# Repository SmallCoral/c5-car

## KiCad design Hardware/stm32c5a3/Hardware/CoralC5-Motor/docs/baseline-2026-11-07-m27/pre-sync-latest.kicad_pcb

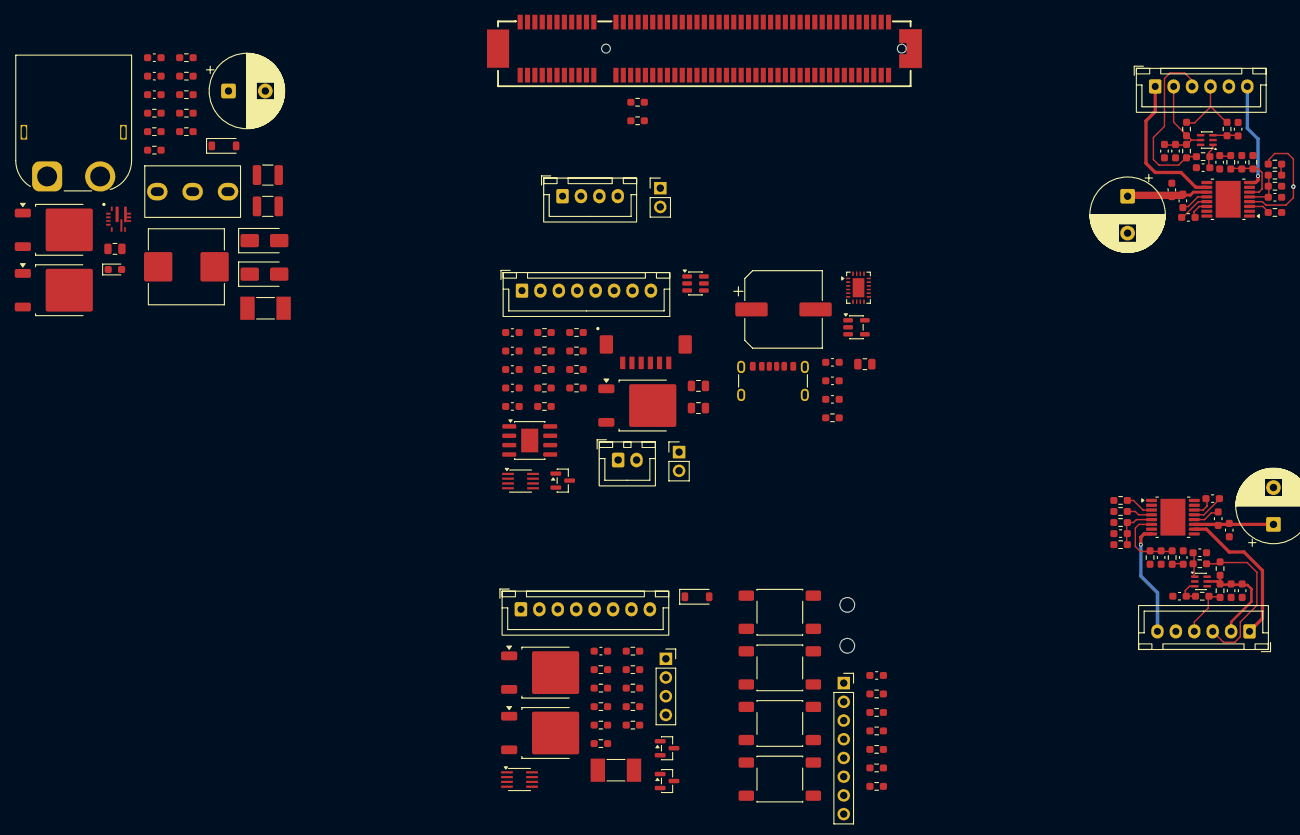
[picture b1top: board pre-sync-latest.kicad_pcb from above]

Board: 2 copper layers, 147 parts (0 on the bottom side), 108 nets.

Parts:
C1, C13, C33: 470u / 25V; Capacitor_THT__CP_Radial_D10.0mm_P5.00mm
C2: 10uF/50V X7R; Capacitor_SMD__C_0805_2012Metric
C3, C72, C76, C79, C80, C82: 100nF/50V; C_0603_1608Metric_Gap0.85mm_HandSolder
C4: 100nF/16V; C_0603_1608Metric_Gap0.85mm_HandSolder
C5, C50: 22uF/25V X7R; Capacitor_SMD__C_1210_3225Metric
C10, C30: 22n / 50V; C_0603_1608Metric_Gap0.85mm_HandSolder
C11, C14, C16, C19, C31, C34, C36, C39: 100n / 16V; C_0603_1608Metric_Gap0.85mm_HandSolder
C12, C32: 100n / 50V; C_0603_1608Metric_Gap0.85mm_HandSolder
C15, C35: 10n / 16V; C_0603_1608Metric_Gap0.85mm_HandSolder
C17, C18, C37, C38: 1n / 16V; C_0603_1608Metric_Gap0.85mm_HandSolder
C20, C40: 1u / 10V; C_0603_1608Metric_Gap0.85mm_HandSolder
C54, C55: 1uF/10V X7R; C_0603_1608Metric_Gap0.85mm_HandSolder
C56: 100nF/10V; C_0603_1608Metric_Gap0.85mm_HandSolder
C62, C78: 10uF/10V; Capacitor_SMD__C_0805_2012Metric
C63: 150pF/50V C0G; C_0603_1608Metric_Gap0.85mm_HandSolder
C73: 12nF/50V; C_0603_1608Metric_Gap0.85mm_HandSolder
C77: 1nF/50V; C_0603_1608Metric_Gap0.85mm_HandSolder
C81: 150uF/16V; Capacitor_SMD__CP_Elec_10x7.9
C83: 10uF/10V X7R; Capacitor_SMD__C_0805_2012Metric
D1: BZT52C12; Diode_SMD__D_SOD-123
D2: SMAJ15A; Diode_SMD__D_SMA
D3: SS34; Diode_SMD__D_SMA
D4: LED_GREEN; LED_0603_1608Metric_Gap0.85mm_HandSolder
D5: 12V; Diode_SMD__D_SOD-123
F1: 15A/85V FAST; Fuse_Littelfuse_448_6.10x2.69mm_GenericBody
F2: 4A / 125V 延时; Fuse_NANO2_454_6.10x2.69mm
H1, H2: TFT孔 D2.0; MountingHole__MountingHole_2mm
J1: XT60PW-M; AMASS_XT60PW-M_1x02_P7.20mm_Horizontal
J4, J6: MG513 / XH2.50 / 6P; Connector_JST__JST_XH_B6B-XH-A_1x06_P2.50mm_Vertical
J8: SWD / XH2.50; Connector_JST__JST_XH_B4B-XH-A_1x04_P2.50mm_Vertical
J10: RUN / STOP_NC; Connector_PinHeader_2.54mm__PinHeader_1x02_P2.54mm_Vertical
J14: C5-EDGE-3 / 98P; C5_EDGE_3_Socket
J15: HC-08_四脚接口; Connector_PinSocket_2.54mm__PinSocket_1x04_P2.54mm_Vertical
J17: TFT_ZJY180S0800TG01; Connector_PinSocket_2.54mm__PinSocket_1x08_P2.54mm_Vertical
J19: MaixCAM2_6P; ZX_MX1.25_6PWT
J20: 灰度并行_CH1-CH8; Connector_JST__JST_XH_B8B-XH-A_1x08_P2.50mm_Vertical
J21: 灰度电源_GND+5V; Connector_JST__JST_XH_B2B-XH-A_1x02_P2.50mm_Vertical
J23: ZDT_XS_TTL_8P; Connector_JST__JST_XH_B8B-XH-A_1x08_P2.50mm_Vertical
J27: 供电使能跳线; Connector_PinHeader_2.54mm__PinHeader_1x02_P2.54mm_Vertical
J28: Action4_USB_C_5V; Connector_USB__USB_C_Receptacle_GCT_USB4125-xx-x_6P_TopMnt_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
L1: 3.3uH / 12A; Inductor_SMD__L_Wuerth_HCI-1050
Q1, Q2, Q5, Q6, Q7: DMP3007LK3-13; Package_TO_SOT_SMD__TO-252-2
Q4, Q9: BSS138BK; Package_TO_SOT_SMD__SOT-23
Q8: MMBT3904; Package_TO_SOT_SMD__SOT-23
R1, R14, R34, R77, R78, R80, R81, R84, R86, R87, R88, R89, R90: 100k; R_0603_1608Metric_Gap0.85mm_HandSolder
R2, R82: 4.7k; R_0603_1608Metric_Gap0.85mm_HandSolder
R3: 82k / 1%; R_0603_1608Metric_Gap0.85mm_HandSolder
R4, R10, R11, R30, R31: 10k / 1%; R_0603_1608Metric_Gap0.85mm_HandSolder
R5: 2.2k; R_0603_1608Metric_Gap0.85mm_HandSolder
R6: 100R; R_0603_1608Metric_Gap0.85mm_HandSolder
R7, R13, R18, R19, R33, R38, R39, R50, R51, R52, R53, R55, R56, R76, R83, R85: 10k; R_0603_1608Metric_Gap0.85mm_HandSolder
R12, R32: 1.82k / 1%; R_0603_1608Metric_Gap0.85mm_HandSolder
R15, R16, R17, R35, R36, R37: 1k; R_0603_1608Metric_Gap0.85mm_HandSolder
R59: 73.8k / 0.1%; R_0603_1608Metric_Gap0.85mm_HandSolder
R60: 10k / 0.1%; R_0603_1608Metric_Gap0.85mm_HandSolder
R68: 33.6k / 0.1%; R_0603_1608Metric_Gap0.85mm_HandSolder
R69, R71: 15k / 0.1%; R_0603_1608Metric_Gap0.85mm_HandSolder
R70: 42.2k / 0.1%; R_0603_1608Metric_Gap0.85mm_HandSolder
R72: 95.3k / 1%; R_0603_1608Metric_Gap0.85mm_HandSolder
R91: 100k / 1%; R_0603_1608Metric_Gap0.85mm_HandSolder
R92: 30.1k / 1%; R_0603_1608Metric_Gap0.85mm_HandSolder
SW1: SS12D10G5; SS12D10G5_SHOUHAN_3P_P4.80mm
SW2: 模式; SW_Push_6x6x4.3mm_SMD_4Pad_Generic
SW3: 下一项; SW_Push_6x6x4.3mm_SMD_4Pad_Generic
SW4: 确认; SW_Push_6x6x4.3mm_SMD_4Pad_Generic
SW5: 启动; SW_Push_6x6x4.3mm_SMD_4Pad_Generic
U1: TPS56837RPAR; Texas_RPA0010A_HotRod_3x3
U2, U4: DRV8874PWPR; DRV8874_PWP0016
U3, U5: SN74LVC2G17DCKR; Package_TO_SOT_SMD__SOT-363_SC-70-6
U7: AP2112K-3.3TRG1; Package_TO_SOT_SMD__SOT-23-5
U10: SGM2531CXPS8G/TR; SGM_PS8_SOIC8_EP2.33x3.22_HandSolder
U13, U15: SN74LVC2G125DCTR; Package_SO__SSOP-8_2.95x2.8mm_P0.65mm
U14: LTC4412ES6#TRMPBF; Package_TO_SOT_SMD__TSOT-23-6
U16: TPS25810RVCR; Package_DFN_QFN__Texas_RVC0020A_WQFN-20-1EP_3x4mm_P0.5mm_EP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

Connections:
/V3V3: C19.1, C20.1, C39.1, C40.1, C76.1, C80.1, J4.2 (VENC), J6.2 (VENC), J8.1, J14.A47 (A47_/_+3V3), J14.B47 (B47_/_+3V3), R10.1, R13.2, R18.1, R19.2, R30.1, R33.2, R38.1, R39.2, R50.1, R51.1, R52.1, R53.1, R76.1, R80.1, R85.1, R88.1, U3.5 (VCC), U5.5 (VCC), U13.8 (VCC), U15.8 (VCC)
/V3V3_EXT: C55.1, C56.1, J15.1 (3V3), J17.2 (VCC_3V3), R55.1, R56.1, U7.5 (VOUT)
/V5_EXT: C5.1, C54.1, C63.1, C72.1, C78.1, C81.1, C82.1, D3.2 (A), J21.2 (+5V), J27.1 (5V), L1.2, R59.1, R70.1, U7.1 (VIN), U7.3 (EN), U10.4 (IN), U16.2 (IN1), U16.3 (IN1), U16.4 (IN2), U16.5 (AUX), U16.6 (EN), U16.7 (CHG), U16.8 (CHG_HI)
/V5_SYS: D3.1 (K), J14.A48 (A48_/_+5V_SYS), J14.B48 (B48_/_+5V_SYS), R5.1
/VM: C1.1, C2.1, C3.1, C11.1, C12.1, C13.1, C31.1, C32.1, C33.1, C50.1, D2.1 (K), F2.1, Q2.2 (D), R3.1, U1.8 (VIN), U2.11 (VM), U4.11 (VM)
/中景园屏幕与四个操作按钮/KEY_MODE: J14.B7 (B7_/_PC4), R50.2, SW2.1
/中景园屏幕与四个操作按钮/KEY_NEXT: J14.B8 (B8_/_PC5), R51.2, SW3.1
/中景园屏幕与四个操作按钮/KEY_OK: J14.B11 (B11_/_PB2), R52.2, SW4.1
/中景园屏幕与四个操作按钮/KEY_START: J14.B12 (B12_/_PE7), R53.2, SW5.1
/中景园屏幕与四个操作按钮/TFT_BL: J14.A32 (A32_/_PB4), J17.8 (BL)
/中景园屏幕与四个操作按钮/TFT_CS: J14.B3 (B3_/_PA4), J17.7 (CS), R55.2
/中景园屏幕与四个操作按钮/TFT_DC: J14.B10 (B10_/_PB1), J17.6 (DC)
/中景园屏幕与四个操作按钮/TFT_MOSI: J14.B6 (B6_/_PA7), J17.4 (SDA)
/中景园屏幕与四个操作按钮/TFT_RES: J14.B9 (B9_/_PB0), J17.5 (RES), R56.2
/中景园屏幕与四个操作按钮/TFT_SCK: J14.B4 (B4_/_PA5), J17.3 (SCL)
/右电机与编码器/MOTOR_RUN: J10.2, R7.1, R14.1, R34.1, U2.3 (nSLEEP), U4.3 (nSLEEP)
/右电机与编码器/R_DIR: J14.A34 (A34_/_PD7), U4.2 (PH/IN2)
/右电机与编码器/R_ENC_A: J14.A33 (A33_/_PB3), U5.6 (1Y)
/右电机与编码器/R_ENC_B: J14.A45 (A45_/_PA15), U5.4 (2Y)
/右电机与编码器/R_ISENSE: C36.1, J14.A11 (A11_/_PC0), R35.2
/右电机与编码器/R_M_OUT1: J6.6 (M+), U4.8 (OUT1)
/右电机与编码器/R_M_OUT2: J6.1 (M-), U4.10 (OUT2)
/右电机与编码器/R_PWM: J14.A27 (A27_/_PB8), U4.1 (EN/IN1)
/右电机与编码器/R_nFAULT: J14.A35 (A35_/_PD6), R33.1, U4.4 (nFAULT)
/四脚蓝牙与外接步进驱动接口/BT_RX: J14.B2 (B2_/_PA3), J15.4 (TXD)
/四脚蓝牙与外接步进驱动接口/BT_TX: J14.A2 (A2_/_PA2), J15.3 (RXD)
/四脚蓝牙与外接步进驱动接口/STEP_PWR_EN: J14.B30 (B30_/_PD12), R83.1
/四脚蓝牙与外接步进驱动接口/STEP_UART_RX: J14.A29 (A29_/_PB7), U15.3 (2Y)
/四脚蓝牙与外接步进驱动接口/STEP_UART_TX: J14.A30 (A30_/_PB6), R88.2, U15.2 (1A)
/四脚蓝牙与外接步进驱动接口/VM_STEP: J23.1 (VM_V+), Q7.2 (D), R86.1
/左电机与编码器/L_DIR: J14.A8 (A8_/_PC3), U2.2 (PH/IN2)
/左电机与编码器/L_ENC_A: J14.A4 (A4_/_PA0), U3.6 (1Y)
/左电机与编码器/L_ENC_B: J14.A3 (A3_/_PA1), U3.4 (2Y)
/左电机与编码器/L_ISENSE: C16.1, J14.A5 (A5_/_PH5), R15.2
/左电机与编码器/L_M_OUT1: J4.6 (M+), U2.8 (OUT1)
/左电机与编码器/L_M_OUT2: J4.1 (M-), U2.10 (OUT2)
/左电机与编码器/L_PWM: J14.A9 (A9_/_PC2), U2.1 (EN/IN1)
/左电机与编码器/L_nFAULT: J14.A7 (A7_/_PH4), R13.1, U2.4 (nFAULT)
/核心板接口/GRAY_CH1: J14.B15 (B15_/_PE10), J20.1 (CH1)
/核心板接口/GRAY_CH2: J14.B16 (B16_/_PE11), J20.2 (CH2)
/核心板接口/GRAY_CH3: J14.B17 (B17_/_PE12), J20.3 (CH3)
/核心板接口/GRAY_CH4: J14.B18 (B18_/_PE13), J20.4 (CH4)
/核心板接口/GRAY_CH5: J14.B19 (B19_/_PE14), J20.5 (CH5)
/核心板接口/GRAY_CH6: J14.B20 (B20_/_PE15), J20.6 (CH6)
/核心板接口/GRAY_CH7: J14.B28 (B28_/_PD10), J20.7 (CH7)
/核心板接口/GRAY_CH8: J14.B29 (B29_/_PD11), J20.8 (CH8)
/核心板接口/MOTOR_EN_REQ: J14.B13 (B13_/_PE8), R6.1
/核心板接口/SWCLK: J8.3, J14.A46 (A46_/_PA14)
/核心板接口/SWDIO: J8.2, J14.B43 (B43_/_PA13)
/核心板接口/VIDEO_RX: J14.B35 (B35_/_PC7), U13.3 (2Y)
/核心板接口/VIDEO_TX: J14.B34 (B34_/_PC6), R80.2, U13.2 (1A)
/灰度与 MaixCAM2 识别/V5_MAIX_PROT: C62.1, J19.2 (5V_IN), Q4.1 (G), Q5.3 (S), R77.1, U14.6 (SENSE)
/输入、总开关与降压/SW_SOURCE: D1.1 (K), Q1.3 (S), Q2.3 (S), R1.2, SW1.1 (A)
GND: C1.2, C2.2, C3.2, C5.2, C12.2, C13.2, C14.2, C15.2, C16.2, C17.1, C18.2, C19.2, C20.2, C32.2, C33.2, C34.2, C35.2, C36.2, C37.1, C38.2, C39.2, C40.2, C50.2, C54.2, C55.2, C56.2, C62.2, C72.2, C73.2, C76.2, C77.2, C78.2, C79.2, C80.2, C81.2, C82.2, C83.2, D2.2 (A), D4.1 (K), J1.2 (GND), J4.5 (GND), J6.5 (GND), J8.4, J14.50 (MP1_/_GND), J14.51 (MP2_/_GND), J14.A1 (A1_/_GND), J14.A49 (A49_/_GND), J14.B1 (B1_/_GND), J14.B49 (B49_/_GND), J15.2 (GND), J17.1 (GND), J19.1 (GND), J19.MP, J21.1 (GND), J23.2 (GND), J28.A12 (GND), J28.B12 (GND), J28.SH (SHIELD), Q4.2 (S), Q8.2 (E), Q9.2 (S), R2.2, R4.2, R7.2, R11.2, R12.2, R14.2, R31.2, R32.2, R34.2, R60.2, R69.2, R71.2, R72.2, R77.2, R78.2, R84.2, R87.2, R89.2, R90.2, R92.2, SW2.2, SW3.2, SW4.2, SW5.2, U1.3 (AGND), U1.9 (PGND), U2.7 (IMODE), U2.9 (PGND), U2.15 (GND), U2.16 (PMODE), U2.17 (EP), U3.2 (GND), U4.7 (IMODE), U4.9 (PGND), U4.15 (GND), U4.16 (PMODE), U4.17 (EP), U5.2 (GND), U7.2 (GND), U10.1 (GND), U10.9 (EP_GND), U13.4 (GND), U14.2 (GND), U14.3 (CTL), U15.4 (GND), U16.12 (GND), U16.21 (EP_GND)
unnamed: C83.1, J28.A9 (VBUS), J28.B9 (VBUS), U16.14 (OUT), U16.15 (OUT)
unnamed: D1.2 (A), Q1.1 (G), Q2.1 (G), R1.1, SW1.2 (B)
unnamed: D4.2 (A), R5.2
unnamed: D5.2 (A), Q6.1 (G), Q7.1 (G)
unnamed: D5.1 (K), Q6.3 (S), Q7.3 (S), R81.1
unnamed: F1.1, J1.1 (BAT+)
unnamed: J4.3 (A), R16.1, R18.2
unnamed: J4.4 (B), R17.1, R19.1
unnamed: J6.3 (A), R36.1, R38.2
unnamed: J6.4 (B), R37.1, R39.1
unnamed: J10.1, R6.2
unnamed: J19.6 (UART4_RX), U13.6 (1Y)
unnamed: J19.5 (UART4_TX), R78.1, U13.5 (2A)
unnamed: J23.7 (R/A/H_RX), R90.1, U15.6 (1Y)
unnamed: J23.8 (T/B/L_TX), R89.1, U15.5 (2A)
unnamed: J27.2 (EN_FEED), R68.1
unnamed: J28.A5 (CC1), U16.11 (CC1)
unnamed: J28.B5 (CC2), U16.13 (CC2)
unnamed: F1.2, Q1.2 (D)
unnamed: Q4.3 (D), R76.2, U13.1 (nOE1), U13.7 (nOE2)
unnamed: C79.1, Q5.2 (D), U10.5 (OUT), U14.1 (VIN)
unnamed: Q5.1 (G), U14.5 (GATE)
unnamed: F2.2, Q6.2 (D)
unnamed: Q8.1 (B), R83.2, R84.1
unnamed: Q8.3 (C), R82.2
unnamed: Q9.3 (D), R85.2, U15.1 (nOE1), U15.7 (nOE2)
unnamed: Q9.1 (G), R86.2, R87.1
unnamed: R81.2, R82.1
unnamed: R2.1, SW1.3 (C)
unnamed: C4.1, U1.7 (BOOT)
unnamed: R3.2, R4.1, U1.1 (EN)
unnamed: C63.2, R59.2, R60.1, U1.2 (FB)
unnamed: R92.1, U1.10 (MODE)
unnamed: C4.2, L1.1, U1.6 (SW)
unnamed: C10.1, U2.13 (CPH)
unnamed: C10.2, U2.14 (CPL)
unnamed: C15.1, R12.1, R15.1, U2.6 (IPROPI)
unnamed: C11.2, U2.12 (VCP)
unnamed: C14.1, R10.2, R11.1, U2.5 (VREF)
unnamed: C17.2, R16.2, U3.1 (1A)
unnamed: C18.1, R17.2, U3.3 (2A)
unnamed: C30.1, U4.13 (CPH)
unnamed: C30.2, U4.14 (CPL)
unnamed: C35.1, R32.1, R35.1, U4.6 (IPROPI)
unnamed: C31.2, U4.12 (VCP)
unnamed: C34.1, R30.2, R31.1, U4.5 (VREF)
unnamed: C37.2, R36.2, U5.1 (1A)
unnamed: C38.1, R37.2, U5.3 (2A)
unnamed: C77.1, R68.2, R69.1, U10.3 (ENUV)
unnamed: R72.1, U10.7 (ILIM)
unnamed: R70.2, R71.1, U10.8 (OVP)
unnamed: C73.1, U10.2 (SS)
unnamed: R91.1, U16.10 (REF)
unnamed: R91.2, U16.9 (REF_RTN)

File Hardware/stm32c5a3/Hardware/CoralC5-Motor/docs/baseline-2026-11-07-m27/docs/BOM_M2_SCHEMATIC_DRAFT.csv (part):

reference,value,mpn,tolerance,footprint,datasheet,sheet,status
C1,470u / 25V,EEU-FR1E471,,Motor:Capacitor_THT__CP_Radial_D10.0mm_P5.00mm,,/输入、总开关与降压/,M2.6 schematic draft; PCB not updated; not production release
C2,10u / 50V,GRM21BR61H106KE43L,,Motor:Capacitor_SMD__C_0805_2012Metric,,/输入、总开关与降压/,M2.6 schematic draft; PCB not updated; not production release
C3,100n / 50V,,,Motor:C_0603_1608Metric_Gap0.85mm_HandSolder,,/输入、总开关与降压/,M2.6 schematic draft; PCB not updated; not production release
C4,100n / 16V,,,Motor:C_0603_1608Metric_Gap0.85mm_HandSolder,,/输入、总开关与降压/,M2.6 schematic draft; PCB not updated; not production release
C5,22u / 10V,GRM31CR71A226KE15L,,Motor:Capacitor_SMD__C_1206_3216Metric,,/输入、总开关与降压/,M2.6 schematic draft; PCB not updated; not production release
C6,22u / 10V,GRM31CR71A226KE15L,,Motor:Capacitor_SMD__C_1206_3216Metric,,/输入、总开关与降压/,M2.6 schematic draft; PCB not updated; not production release
C10,22n / 50V,,,Motor:C_0603_1608Metric_Gap0.85mm_HandSolder,,/左电机与编码器/,M2.6 schematic draft; PCB not updated; not production release
C11,100n / 16V,,,Motor:C_0603_1608Metric_Gap0.85mm_HandSolder,,/左电机与编码器/,M2.6 schematic draft; PCB not updated; not production release
C12,100n / 50V,,,Motor:C_0603_1608Metric_Gap0.85mm_HandSolder,,/左电机与编码器/,M2.6 schematic draft; PCB not updated; not production release
C13,470u / 25V,EEU-FR1E471,,Motor:Capacitor_THT__CP_Radial_D10.0mm_P5.00mm,,/左电机与编码器/,M2.6 schematic draft; PCB not updated; not production release
C14,100n / 16V,,,Motor:C_0603_1608Metric_Gap0.85mm_HandSolder,,/左电机与编码器/,M2.6 schematic draft; PCB not updated; not production release
C15,10n / 16V,,,Motor:C_0603_1608Metric_Gap0.85mm_HandSolder,,/左电机与编码器/,M2.6 schematic draft; PCB not updated; not production release
C16,100n / 16V,,,Motor:C_0603_1608Metric_Gap0.85mm_HandSolder,,/左电机与编码器/,M2.6 schematic draft; PCB not updated; not production release
C17,1n / 16V,,,Motor:C_0603_1608Metric_Gap0.85mm_HandSolder,,/左电机与编码器/,M2.6 schematic draft; PCB not updated; not production release
C18,1n / 16V,,,Motor:C_0603_1608Metric_Gap0.85mm_HandSolder,,/左电机与编码器/,M2.6 schematic draft; PCB not updated; not production release
C19,100n / 16V,,,Motor:C_0603_1608Metric_Gap0.85mm_HandSolder,,/左电机与编码器/,M2.6 schematic draft; PCB not updated; not production release
C20,1u / 10V,,,Motor:C_0603_1608Metric_Gap0.85mm_HandSolder,,/左电机与编码器/,M2.6 schematic draft; PCB not updated; not production release
C30,22n / 50V,,,Motor:C_0603_1608Metric_Gap0.85mm_HandSolder,,/右电机与编码器/,M2.6 schematic draft; PCB not updated; not production release
C31,100n / 16V,,,Motor:C_0603_1608Metric_Gap0.85mm_HandSolder,,/右电机与编码器/,M2.6 schematic draft; PCB not updated; not production release
C32,100n / 50V,,,Motor:C_0603_1608Metric_Gap0.85mm_HandSolder,,/右电机与编码器/,M2.6 schematic draft; PCB not updated; not production release
C33,470u / 25V,EEU-FR1E471,,Motor:Capacitor_THT__CP_Radial_D10.0mm_P5.00mm,,/右电机与编码器/,M2.6 schematic draft; PCB not updated; not production release
C34,100n / 16V,,,Motor:C_0603_1608Metric_Gap0.85mm_HandSolder,,/右电机与编码器/,M2.6 schematic draft; PCB not updated; not production release
C35,10n / 16V,,,Motor:C_0603_1608Metric_Gap0.85mm_HandSolder,,/右电机与编码器/,M2.6 schematic draft; PCB not updated; not production release
C36,100n / 16V,,,Motor:C_0603_1608Metric_Gap0.85mm_HandSolder,,/右电机与编码器/,M2.6 schematic draft; PCB not updated; not production release
C37,1n / 16V,,,Motor:C_0603_1608Metric_Gap0.85mm_HandSolder,,/右电机与编码器/,M2.6 schematic draft; PCB not updated; not production release
C38,1n / 16V,,,Motor:C_0603_1608Metric_Gap0.85mm_HandSolder,,/右电机与编码器/,M2.6 schematic draft; PCB not updated; not production release
C39,100n / 16V,,,Motor:C_0603_1608Metric_Gap0.85mm_HandSolder,,/右电机与编码器/,M2.6 schematic draft; PCB not updated; not production release
C40,1u / 10V,,,Motor:C_0603_1608Metric_Gap0.85mm_HandSolder,,/右电机与编码器/,M2.6 schematic draft; PCB not updated; not production release
C50,10uF/25V X7R,,,Motor:Capacitor_SMD__C_1206_3216Metric,,/外设独立五伏与三伏三供电/,M2.6 schematic draft; PCB not updated; not production release
C51,100nF/50V,,,Motor:C_0603_1608Metric_Gap0.85mm_HandSolder,,/外设独立五伏与三伏三供电/,M2.6 schematic draft; PCB not updated; not production release
C52,22uF/10V X7R,,,Motor:Capacitor_SMD__C_1206_3216Metric,,/外设独立五伏与三伏三供电/,M2.6 schematic draft; PCB not updated; not production release
C53,22uF/10V X7R,,,Motor:Capacitor_SMD__C_1206_3216Metric,,/外设独立五伏与三伏三供电/,M2.6 schematic draft; PCB not updated; not production release
C54,1uF/10V X7R,,,Motor:C_0603_1608Metric_Gap0.85mm_HandSolder,,/外设独立五伏与三伏三供电/,M2.6 schematic draft; PCB not updated; not production release
C55,1uF/10V X7R,,,Motor:C_0603_1608Metric_Gap0.85mm_HandSolder,,/外设独立五伏与三伏三供电/,M2.6 schematic draft; PCB not updated; not production release
C56,100nF/10V,,,Motor:C_0603_1608Metric_Gap0.85mm_HandSolder,,/中景园屏幕与四个操作按钮/,M2.6 schematic draft; PCB not updated; not production release
C57,100nF,,,Motor:C_0603_1608Metric_Gap0.85mm_HandSolder,,/中景园屏幕与四个操作按钮/,M2.6 schematic draft; PCB not updated; not production release
C58,100nF,,,Motor:C_0603_1608Metric_Gap0.85mm_HandSolder,,/中景园屏幕与四个操作按钮/,M2.6 schematic draft; PCB not updated; not production release
C59,100nF,,,Motor:C_0603_1608Metric_Gap0.85mm_HandSolder,,/中景园屏幕与四个操作按钮/,M2.6 schematic draft; PCB not updated; not production release
C60,100nF,,,Motor:C_0603_1608Metric_Gap0.85mm_HandSolder,,/中景园屏幕与四个操作按钮/,M2.6 schematic draft; PCB not updated; not production release
C62,10uF/10V,,,Motor:Capacitor_SMD__C_0805_2012Metric,,/八路灰度与图传像头模块接口/,M2.6 schematic draft; PCB not updated; not production release
C63,47pF/50V C0G,,,Motor:C_0603_1608Metric_Gap0.85mm_HandSolder,,/外设独立五伏与三伏三供电/,M2.6 schematic draft; PCB not updated; not production release
C72,100nF/50V,,,Motor:C_0603_1608Metric_Gap0.85mm_HandSolder,,/八路灰度与图传像头模块接口/,M2.6 schematic draft; PCB not updated; not production release
C73,12nF/50V,,,Motor:C_0603_1608Metric_Gap0.85mm_HandSolder,,/八路灰度与图传像头模块接口/,M2.6 schematic draft; PCB not updated; not production release
C76,100nF/50V,,,Motor:C_0603_1608Metric_Gap0.85mm_HandSolder,,/八路灰度与图传像头模块接口/,M2.6 schematic draft; PCB not updated; not production release
C77,1nF/50V,,,Motor:C_0603_1608Metric_Gap0.85mm_HandSolder,,/八路灰度与图传像头模块接口/,M2.6 schematic draft; PCB not updated; not production release
C78,10uF/10V,,,Motor:Capacitor_SMD__C_0805_2012Metric,,/八路灰度与图传像头模块接口/,M2.6 schematic draft; PCB not updated; not production release
C79,100nF/50V,,,Motor:C_0603_1608Metric_Gap0.85mm_HandSolder,,/八路灰度与图传像头模块接口/,M2.6 schematic draft; PCB not updated; not production release
C80,100nF/50V,,,Motor:C_0603_1608Metric_Gap0.85mm_HandSolder,,/四脚蓝牙与外接步进驱动接口/,M2.6 schematic draft; PCB not updated; not production release
D1,BZT52C12,BZT52C12,,Motor:Diode_SMD__D_SOD-123,,/输入、总开关与降压/,M2.6 schematic draft; PCB not updated; not production release
D2,SMAJ15A,SMAJ15A,,Motor:Diode_SMD__D_SMA,,/输入、总开关与降压/,M2.6 schematic draft; PCB not updated; not production release
D3,SS34,SS34,,Motor:Diode_SMD__D_SMA,,/输入、总开关与降压/,M2.6 schematic draft; PCB not updated; not production release
D4,LED_GREEN,LTST-C190KGKT,,Motor:LED_0603_1608Metric_Gap0.85mm_HandSolder,,/输入、总开关与降压/,M2.6 schematic draft; PCB not updated; not production release
D5,12V,"BZT52-C12,115",,Motor:Diode_SMD__D_SOD-123,https://assets.nexperia.com/documents/data-sheet/BZT52_SER.pdf,/四脚蓝牙与外接步进驱动接口/,M2.6 schematic draft; PCB not updated; not production release
F1,15A/85V FAST,0448015.MR,,Motor:Fuse_Littelfuse_448_6.10x2.69mm_GenericBody,https://www.littelfuse.com/assetdocs/littelfuse_fuse_448_dat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,/输入、总开关与降压/,M2.6 schematic draft; PCB not updated; not production release
F2,4A / 125V 延时,0454004.MR,,Motor:Fuse_NANO2_454_6.10x2.69mm,https://www.littelfuse.com/assetdocs/fuse-452-and-454-datash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,/四脚蓝牙与外接步进驱动接口/,M2.6 schematic draft; PCB not updated; not production release
J1,XT60PW-M,XT60PW-M,,Motor:AMASS_XT60PW-M_1x02_P7.20mm_Horizontal,https://www.china-amass.com/biao/289.html,/输入、总开关与降压/,M2.6 schematic draft; PCB not updated; not production release
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
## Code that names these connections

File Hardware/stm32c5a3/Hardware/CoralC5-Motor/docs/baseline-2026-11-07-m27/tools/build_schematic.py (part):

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    for pn,name in netmap.items():page.netpin(pins[pn],name)

used={
 'PD12':'L_PWM','PD10':'L_DIR','PD13':'R_PWM','PD11':'R_DIR','PE2':'MOTOR_EN_REQ',
 'PE4':'L_nFAULT','PE5':'R_nFAULT','PA0':'L_ISENSE','PA1':'R_ISENSE',
 'PA15':'L_ENC_A','PB3':'L_ENC_B','PC6':'R_ENC_A','PC7':'R_ENC_B',
 'PA13':'SWDIO','PA14':'SWCLK','PB6':'AUX_I2C_SCL','PB7':'AUX_I2C_SDA',
 'PA2':'AUX_UART_TX','PA3':'AUX_UART_RX','PA4':'AUX_ADC','PA5':'AUX_GPIO',
 '+3V3':'V3V3','+5V_SYS':'V5_SYS','GND':'GND','NRST':'NRST'}
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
